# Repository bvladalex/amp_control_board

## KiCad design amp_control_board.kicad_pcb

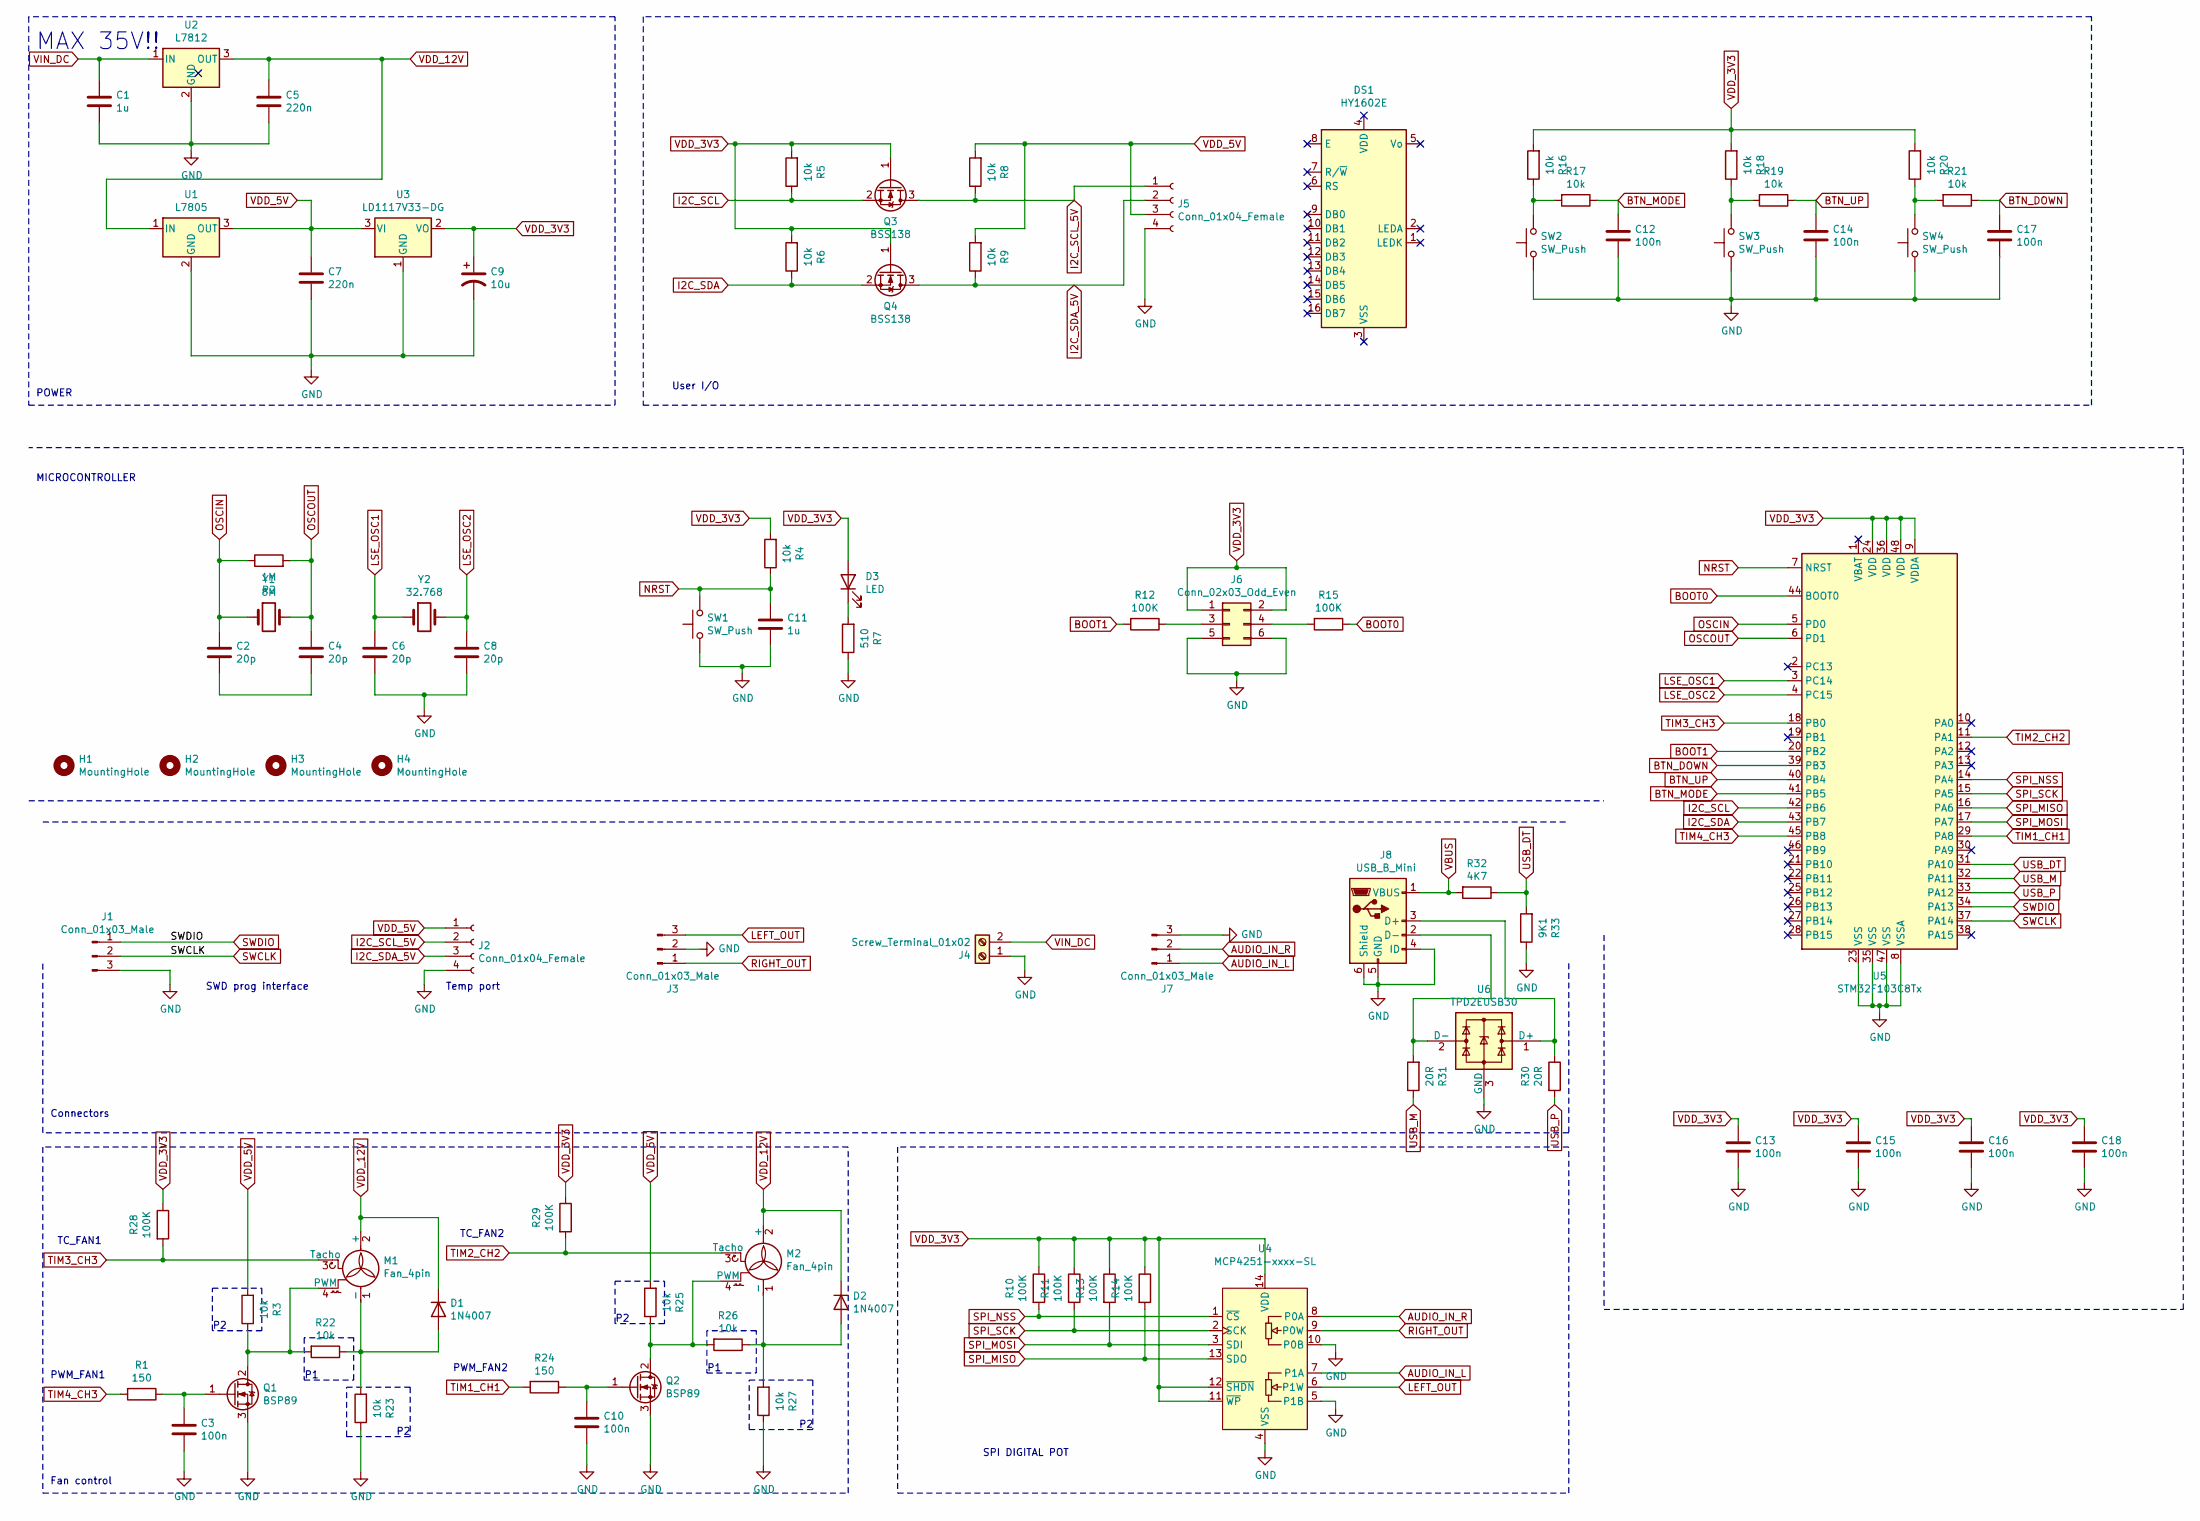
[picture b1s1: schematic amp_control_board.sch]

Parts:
C1: 1u; CP_Elec_10x12.5
C2, C4, C6, C8: 20p; R_0805_2012Metric_Pad1.20x1.40mm_HandSolder
C3, C10, C12, C14, C17: 100n; R_0805_2012Metric_Pad1.20x1.40mm_HandSolder
C5, C7: 220n; CP_Elec_10x10
C9: 10u; CP_Elec_10x10
C11: 1u; R_0805_2012Metric_Pad1.20x1.40mm_HandSolder
C13, C15, C16, C18: 100n; R_0402_1005Metric_Pad0.72x0.64mm_HandSolder
D1, D2: 1N4007; D_3220_8050Metric_Pad2.65x5.15mm_HandSolder
D3: LED; LED_0603_1608Metric
DS1: HY1602E; WC1602A
H1, H2, H3, H4: MountingHole; MountingHole_2.5mm_Pad
J1, J3, J7: Conn_01x03_Male; PinHeader_1x03_P2.54mm_Vertical
J2, J5: Conn_01x04_Female; PinHeader_1x04_P2.54mm_Vertical
J4: Screw_Terminal_01x02; TerminalBlock_bornier-2_P5.08mm
J6: Conn_02x03_Odd_Even; PinHeader_2x03_P2.54mm_Vertical
J8: USB_B_Mini; USB_Mini-B_Lumberg_2486_01_Horizontal
M1, M2: Fan_4pin; PinHeader_1x04_P2.54mm_Vertical
Q1, Q2: BSP89; SOT-223-3_TabPin2
Q3, Q4: BSS138; SOT-23
R1, R24: 150; R_0805_2012Metric_Pad1.20x1.40mm_HandSolder
R2: 1M; R_0805_2012Metric_Pad1.20x1.40mm_HandSolder
R3, R4, R5, R6, R8, R9, R16, R17, R18, R19, R20, R21, R25: 10k; R_0805_2012Metric_Pad1.20x1.40mm_HandSolder
R7: 510; R_0805_2012Metric_Pad1.20x1.40mm_HandSolder
R10, R11, R12, R13, R14, R15, R28, R29: 100K; R_0805_2012Metric_Pad1.20x1.40mm_HandSolder
R22, R23, R26, R27: 10k; R_0402_1005Metric
R30, R31: 20R; R_0402_1005Metric_Pad0.72x0.64mm_HandSolder
R32: 4K7; R_0805_2012Metric_Pad1.20x1.40mm_HandSolder
R33: 9K1; R_0805_2012Metric_Pad1.20x1.40mm_HandSolder
SW1: SW_Push; SW_SPST_EVQPE1
SW2, SW3, SW4: SW_Push; PinHeader_1x02_P2.54mm_Vertical
U1: L7805; TO-252-2
U2: L7812; TO-220-3_Vertical
U3: LD1117V33-DG; TO-252-2
U4: MCP4251-xxxx-SL; SOIC-14_3.9x8.7mm_P1.27mm
U5: STM32F103C8Tx; LQFP-48_7x7mm_P0.5mm
U6: TPD2EUSB30; Texas_DRT-3
Y1: 8M; Crystal_HC49-U_Vertical
Y2: 32.768; Crystal_C38-LF_D3.0mm_L8.0mm_Horizontal_1EP_style2

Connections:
AUDIO_IN_L: J7.1, U4.7 (P1A)
AUDIO_IN_R: J7.2, U4.8 (P0A)
BOOT0: R15.1, U5.44 (BOOT0)
BOOT1: R12.2, U5.20 (PB2)
BTN_DOWN: C17.1, R21.1, U5.39 (PB3)
BTN_MODE: C12.1, R17.1, U5.41 (PB5)
BTN_UP: C14.1, R19.1, U5.40 (PB4)
GND: C1.2, C3.2, C5.2, C6.2, C7.2, C8.2, C9.2, C10.2, C11.2, C12.2, C13.2, C14.2, C15.2, C16.2, C17.2, C18.2, J1.3, J2.4, J3.2, J4.1, J5.4, J6.5, J6.6, J7.3, J8.4 (ID), J8.5 (GND), J8.6 (Shield), Q1.3 (S), Q2.3 (S), R7.1, R23.1, R27.1, R33.1, SW1.1, SW2.1, SW3.1, SW4.1, U1.2 (GND), U2.2 (GND), U3.1 (GND), U4.4 (VSS), U4.5 (P1B), U4.10 (P0B), U5.8 (VSSA), U5.23 (VSS), U5.35 (VSS), U5.47 (VSS), U6.3 (GND)
I2C_SCL: Q3.2 (S), R5.1, U5.42 (PB6)
I2C_SCL_5V: J2.2, J5.1, Q3.3 (D), R8.1
I2C_SDA: Q4.2 (S), R6.1, U5.43 (PB7)
I2C_SDA_5V: J2.3, J5.2, Q4.3 (D), R9.1
LEFT_OUT: J3.3, U4.6 (P1W)
LSE_OSC1: C6.1, U5.3 (PC14), Y2.1
LSE_OSC2: C8.1, U5.4 (PC15), Y2.2
NRST: C11.1, R4.1, SW1.2, U5.7 (NRST)
unnamed: C2.2, C4.2
unnamed: C3.1, Q1.1 (G), R1.1
unnamed: C10.1, Q2.1 (G), R24.1
unnamed: D1.2 (A), M1.1 (-), R22.1, R23.2
unnamed: D2.2 (A), M2.1 (-), R26.1, R27.2
unnamed: D3.1 (K), R7.2
unnamed: J6.3, R12.1
unnamed: J6.4, R15.2
unnamed: J8.2 (D-), R31.2, U6.2 (D-)
unnamed: J8.3 (D+), R30.1, U6.1 (D+)
unnamed: M1.4 (PWM), Q1.2 (D), R3.1, R22.2
unnamed: M2.4 (PWM), Q2.2 (D), R25.1, R26.2
unnamed: R16.1, R17.2, SW2.2
unnamed: R18.1, R19.2, SW3.2
unnamed: R20.1, R21.2, SW4.2
OSCIN: C2.1, R2.1, U5.5 (PD0), Y1.1
OSCOUT: C4.1, R2.2, U5.6 (PD1), Y1.2
RIGHT_OUT: J3.1, U4.9 (P0W)
SPI_MISO: R14.2, U4.13 (SDO), U5.16 (PA6)
SPI_MOSI: R13.2, U4.3 (SDI), U5.17 (PA7)
SPI_NSS: R10.2, U4.1 (~CS), U5.14 (PA4)
SPI_SCK: R11.2, U4.2 (SCK), U5.15 (PA5)
SWCLK: J1.2, U5.37 (PA14)
SWDIO: J1.1, U5.34 (PA13)
TIM1_CH1: R24.2, U5.29 (PA8)
TIM2_CH2: M2.3 (Tacho), R29.2, U5.11 (PA1)
TIM3_CH3: M1.3 (Tacho), R28.2, U5.18 (PB0)
TIM4_CH3: R1.2, U5.45 (PB8)
USB_DT: R32.1, R33.2, U5.31 (PA10)
USB_M: R31.1, U5.32 (PA11)
USB_P: R30.2, U5.33 (PA12)
VBUS: J8.1 (VBUS), R32.2
VDD_3V3: C9.1, C13.1, C15.1, C16.1, C18.1, D3.2 (A), J6.1, J6.2, Q3.1 (G), Q4.1 (G), R4.2, R5.2, R6.2, R10.1, R11.1, R13.1, R14.1, R16.2, R18.2, R20.2, R28.1, R29.1, U3.2 (VO), U4.11 (~WP), U4.12 (~SHDN), U4.14 (VDD), U5.9 (VDDA), U5.24 (VDD), U5.36 (VDD), U5.48 (VDD)
VDD_5V: C7.1, J2.1, J5.3, R3.2, R8.2, R9.2, R25.2, U1.3 (OUT), U3.3 (VI)
VDD_12V: C5.1, D1.1 (K), D2.1 (K), M1.2 (+), M2.2 (+), U1.1 (IN), U2.3 (OUT)
VIN_DC: C1.1, J4.2, U2.1 (IN)

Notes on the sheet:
POWER
Connectors
MICROCONTROLLER
MAX 35V!!
SPI DIGITAL POT
Temp port
User I/O
Fan control
SWD prog interface
TC_FAN1
TC_FAN2
PWM_FAN1
PWM_FAN2

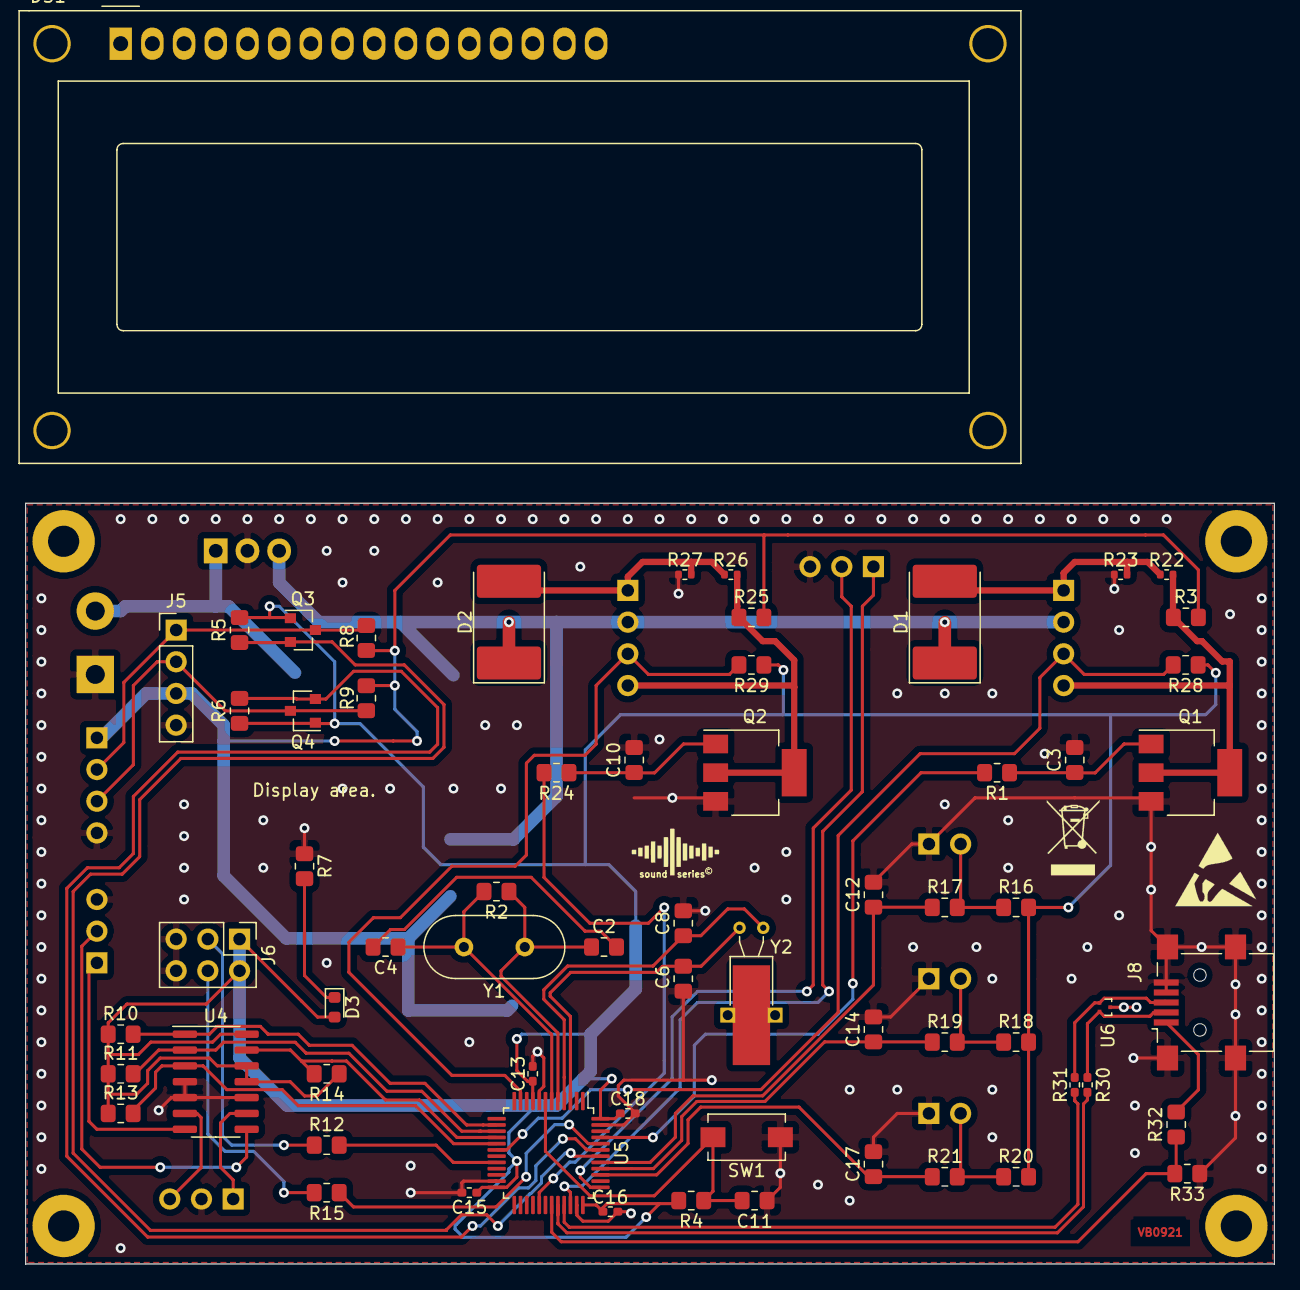
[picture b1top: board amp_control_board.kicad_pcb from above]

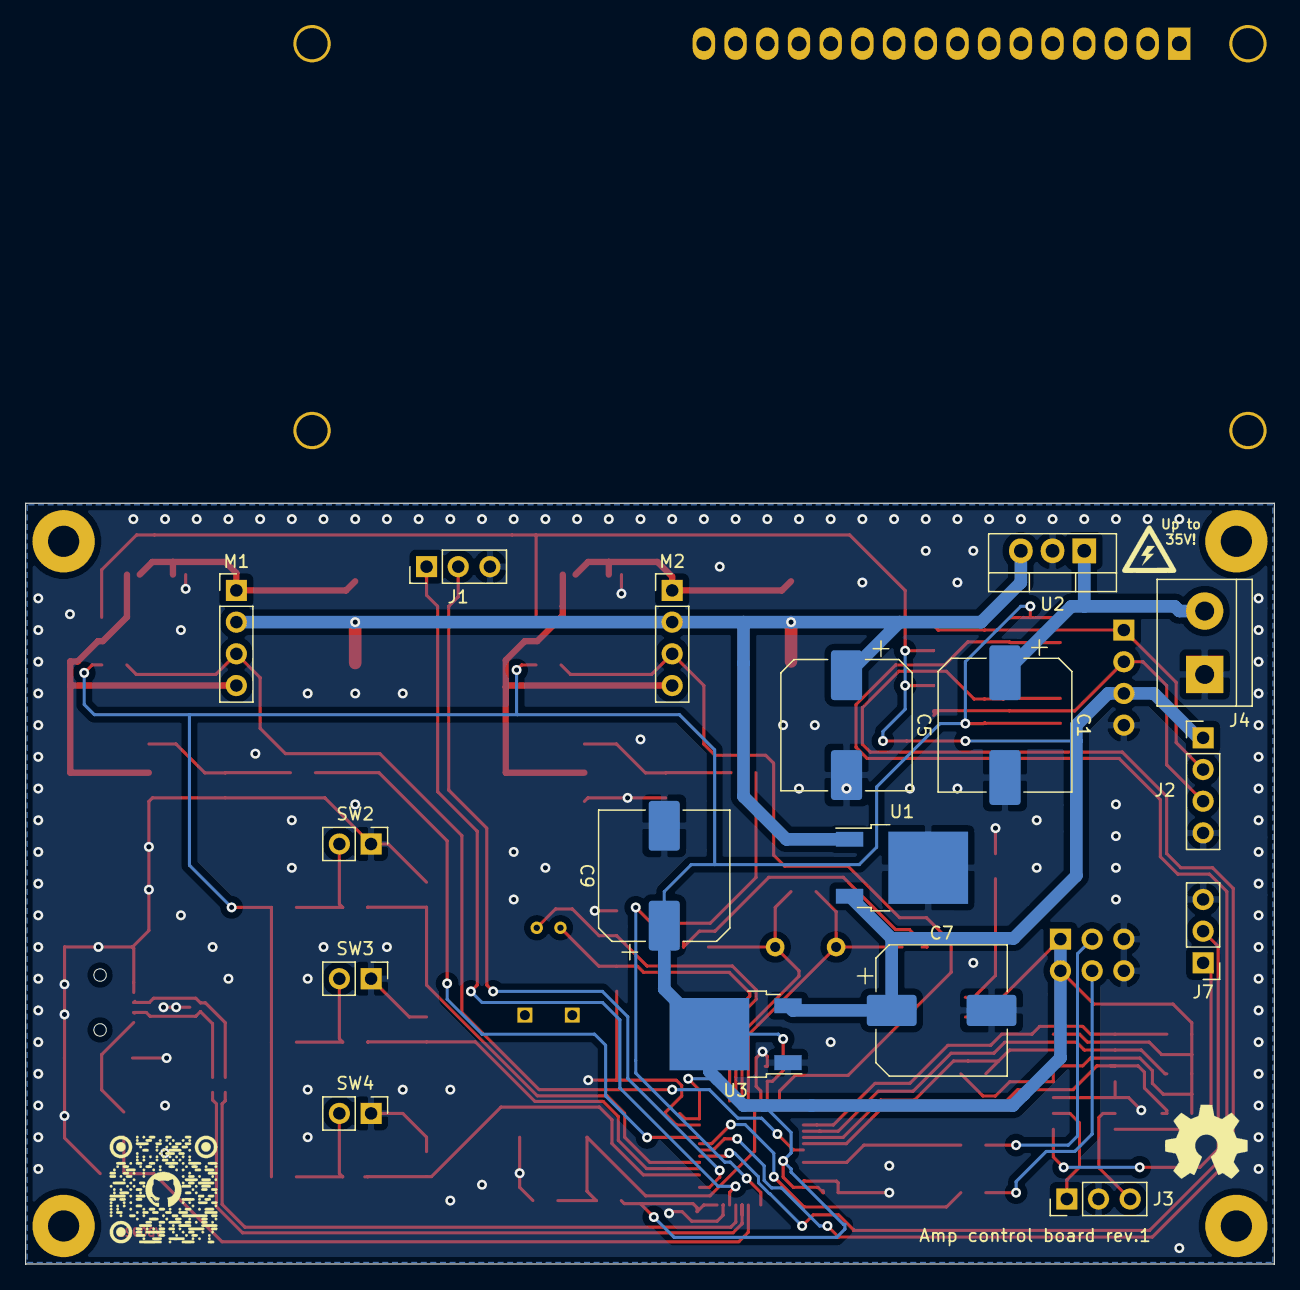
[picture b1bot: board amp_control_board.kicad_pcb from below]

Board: 2 copper layers, 100.1 x 61.0 mm, 85 parts (17 on the bottom side), 52 nets.

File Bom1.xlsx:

RefDes | Value | Package | Status
U5 | STM32F103C8Tx | Package_QFP:LQFP-48_7x7mm_P0.5mm
C16 | 100n | Resistor_SMD:R_0805_2012Metric_Pad1.20x1.40mm_HandSolder
C18 | 100n | Resistor_SMD:R_0805_2012Metric_Pad1.20x1.40mm_HandSolder
Y1 | 8M | Crystal:Crystal_HC49-U_Vertical
C2 | 20p | Resistor_SMD:R_0805_2012Metric_Pad1.20x1.40mm_HandSolder
C4 | 20p | Resistor_SMD:R_0805_2012Metric_Pad1.20x1.40mm_HandSolder
Y2 | 32.768 | Crystal:Crystal_C38-LF_D3.0mm_L8.0mm_Horizontal_1EP_style2
C6 | 20p | Resistor_SMD:R_0805_2012Metric_Pad1.20x1.40mm_HandSolder
C8 | 20p | Resistor_SMD:R_0805_2012Metric_Pad1.20x1.40mm_HandSolder
R2 | 1M | Resistor_SMD:R_0805_2012Metric_Pad1.20x1.40mm_HandSolder
J1 | Conn_01x03_Male | Connector_PinHeader_2.54mm:PinHeader_1x03_P2.54mm_Vertical
C13 | 100n | Resistor_SMD:R_0805_2012Metric_Pad1.20x1.40mm_HandSolder
C15 | 100n | Resistor_SMD:R_0805_2012Metric_Pad1.20x1.40mm_HandSolder
SW1 | SW_Push | Button_Switch_SMD:SW_SPST_EVQPE1
C11 | 1u | Resistor_SMD:R_0805_2012Metric_Pad1.20x1.40mm_HandSolder
R4 | 10k | Resistor_SMD:R_0805_2012Metric_Pad1.20x1.40mm_HandSolder
D3 | LED | LED_SMD:LED_0603_1608Metric
R7 | 510 | Resistor_SMD:R_0805_2012Metric_Pad1.20x1.40mm_HandSolder
J6 | Conn_02x03_Odd_Even | Connector_PinHeader_2.54mm:PinHeader_2x03_P2.54mm_Vertical
R12 | 100K | Resistor_SMD:R_0805_2012Metric_Pad1.20x1.40mm_HandSolder
R15 | 100K | Resistor_SMD:R_0805_2012Metric_Pad1.20x1.40mm_HandSolder
U1 | L7805 | Package_TO_SOT_SMD:TO-252-2
U3 | LD1117V33-DG | Package_TO_SOT_SMD:TO-252-2
C9 | 10u | Capacitor_SMD:C_0805_2012Metric_Pad1.18x1.45mm_HandSolder
U4 | MCP4251-xxxx-SL | Package_SO:SOIC-14_3.9x8.7mm_P1.27mm
J5 | Conn_01x04_Female | Connector_PinHeader_2.54mm:PinHeader_1x04_P2.54mm_Vertical
J2 | Conn_01x04_Female | Connector_PinHeader_2.54mm:PinHeader_1x04_P2.54mm_Vertical
Q3 | BSS138 | Package_TO_SOT_SMD:SOT-23
R5 | 10k | Resistor_SMD:R_0805_2012Metric_Pad1.20x1.40mm_HandSolder
R8 | 10k | Resistor_SMD:R_0805_2012Metric_Pad1.20x1.40mm_HandSolder
Q4 | BSS138 | Package_TO_SOT_SMD:SOT-23
R6 | 10k | Resistor_SMD:R_0805_2012Metric_Pad1.20x1.40mm_HandSolder
R9 | 10k | Resistor_SMD:R_0805_2012Metric_Pad1.20x1.40mm_HandSolder
DS1 | HY1602E | Display:WC1602A
SW2 | SW_Push | Connector_PinHeader_2.54mm:PinHeader_1x02_P2.54mm_Vertical
R16 | 10k | Resistor_SMD:R_0805_2012Metric_Pad1.20x1.40mm_HandSolder
R17 | 10k | Resistor_SMD:R_0805_2012Metric_Pad1.20x1.40mm_HandSolder
C12 | 100n | Resistor_SMD:R_0805_2012Metric_Pad1.20x1.40mm_HandSolder
SW3 | SW_Push | Connector_PinHeader_2.54mm:PinHeader_1x02_P2.54mm_Vertical
R18 | 10k | Resistor_SMD:R_0805_2012Metric_Pad1.20x1.40mm_HandSolder
R19 | 10k | Resistor_SMD:R_0805_2012Metric_Pad1.20x1.40mm_HandSolder
C14 | 100n | Resistor_SMD:R_0805_2012Metric_Pad1.20x1.40mm_HandSolder
SW4 | SW_Push | Connector_PinHeader_2.54mm:PinHeader_1x02_P2.54mm_Vertical
R20 | 10k | Resistor_SMD:R_0805_2012Metric_Pad1.20x1.40mm_HandSolder
R21 | 10k | Resistor_SMD:R_0805_2012Metric_Pad1.20x1.40mm_HandSolder
C17 | 100n | Resistor_SMD:R_0805_2012Metric_Pad1.20x1.40mm_HandSolder
J4 | Screw_Terminal_01x02 | TerminalBlock:TerminalBlock_bornier-2_P5.08mm
J3 | Screw_Terminal_01x03 | TerminalBlock:TerminalBlock_bornier-3_P5.08mm
J7 | AudioJack3_Ground
M1 | Fan_3pin
D1 | 1N4007 | Diode_THT:D_DO-41_SOD81_P10.16mm_Horizontal
Q1 | BSP89 | Package_TO_SOT_SMD:SOT-223-3_TabPin2
R1 | 150 | Resistor_SMD:R_0805_2012Metric_Pad1.20x1.40mm_HandSolder
M2 | Fan_3pin
D2 | 1N4007 | Diode_THT:D_DO-41_SOD81_P10.16mm_Horizontal
Q2 | BSP89 | Package_TO_SOT_SMD:SOT-223-3_TabPin2
R3 | 150 | Resistor_SMD:R_0805_2012Metric_Pad1.20x1.40mm_HandSolder
U2 | MC78M05_TO252 | Package_TO_SOT_SMD:TO-252-2
R10 | 100K | Resistor_SMD:R_0805_2012Metric_Pad1.20x1.40mm_HandSolder
R11 | 100K | Resistor_SMD:R_0805_2012Metric_Pad1.20x1.40mm_HandSolder
R13 | 100K | Resistor_SMD:R_0805_2012Metric_Pad1.20x1.40mm_HandSolder
R14 | 100K | Resistor_SMD:R_0805_2012Metric_Pad1.20x1.40mm_HandSolder
C1 | 1u | Capacitor_SMD:C_0805_2012Metric_Pad1.18x1.45mm_HandSolder
C7 | 220n | Capacitor_SMD:C_0805_2012Metric_Pad1.18x1.45mm_HandSolder
C5 | 220n | Capacitor_SMD:C_0805_2012Metric_Pad1.18x1.45mm_HandSolder
C3 | 100n | Resistor_SMD:R_0805_2012Metric_Pad1.20x1.40mm_HandSolder
C10 | 100n | Resistor_SMD:R_0805_2012Metric_Pad1.20x1.40mm_HandSolder

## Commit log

2021-08-13 first version of amp control board in kicad
2021-08-16 created pcb prj
2021-08-17 changing dev pc
2021-08-17 started floorplan
2021-08-20 Adding changes 2008
2021-08-20 finished floorplan of top layer
2021-08-21 completed preliminary floorplan for both top and bottom
2021-08-21 routeed power for bottom plane
2021-08-22 top routing about 70% done
2021-08-23 routed some more on top layer, added USB interface
2021-08-24 finished routing logic
2021-08-25 90% routing done
2021-08-26 top routing done expect for maybe USB protection
2021-08-31 added USB protection
2021-08-31 finished routing, need to place stiching vias
2021-09-02 silkscreen more or less done.
2021-09-04 project as sent to production
2021-10-17 small cleanup
